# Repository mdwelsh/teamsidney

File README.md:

# sidney-projects

Set up Mac:

sudo easy_install pip
pip install --user pygame

Unicorn HAT Simulator:

https://github.com/jayniz/unicorn-hat-sim

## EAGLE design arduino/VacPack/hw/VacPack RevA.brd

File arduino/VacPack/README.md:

MicroPython on ESP32:
http://docs.micropython.org/en/v1.10/esp32/tutorial/intro.html

Firmware:
https://micropython.org/download/esp32/

```bash
pip install esptool
esptool.py --port /dev/tty.SLAB_USBtoUART erase_flash
esptool.py --chip esp32 --port /dev/tty.SLAB_USBtoUART write_flash -z 0x1000 esp32-idf3-20191220-v1.12.bin
brew install picocom
picocom /dev/tty.SLAB_USBtoUART -b115200

>>> import webrepl_setup
>>> import network
>>> wlan = network.WLAN(network.STA_IF)
>>> wlan.active(True)
>>> wlan.connect('theonet', 'j********')
>>> webrepl.stop()
>>> webrepl.start()
```

Visit:
http://micropython.org/webrepl/#192.168.86.152:8266

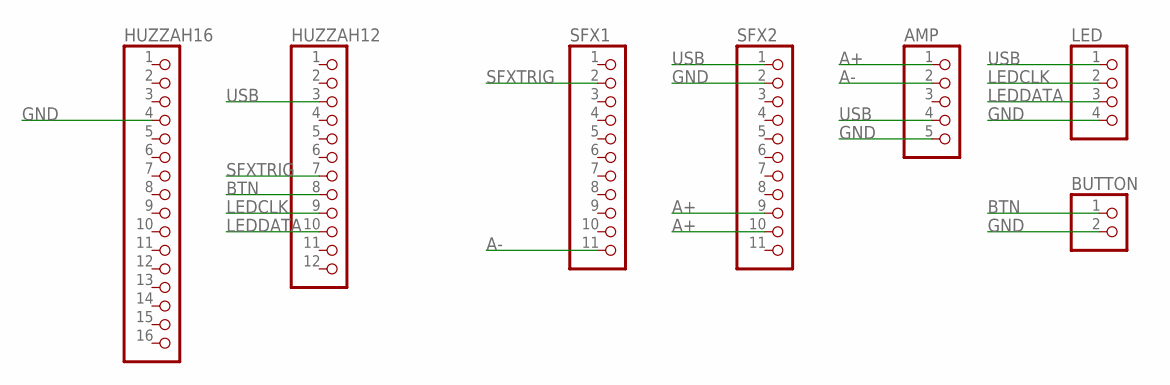
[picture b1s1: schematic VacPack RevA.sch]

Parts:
AMP: PINHD-1X5; 1X05
BUTTON: PINHD-1X2; 1X02
HUZZAH12: PINHD-1X12; 1X12
HUZZAH16: PINHD-1X16; 1X16
LED: PINHD-1X4; 1X04
SFX1, SFX2: PINHD-1X11; 1X11

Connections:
A+: AMP.1, SFX2.9, SFX2.10
A-: AMP.2, SFX1.11
BTN: BUTTON.1, HUZZAH12.8
GND: AMP.5, BUTTON.2, HUZZAH16.4, LED.4, SFX2.2
LEDCLK: HUZZAH12.9, LED.2
LEDDATA: HUZZAH12.10, LED.3
SFXTRIG: HUZZAH12.7, SFX1.2
USB: AMP.4, HUZZAH12.3, LED.1, SFX2.1

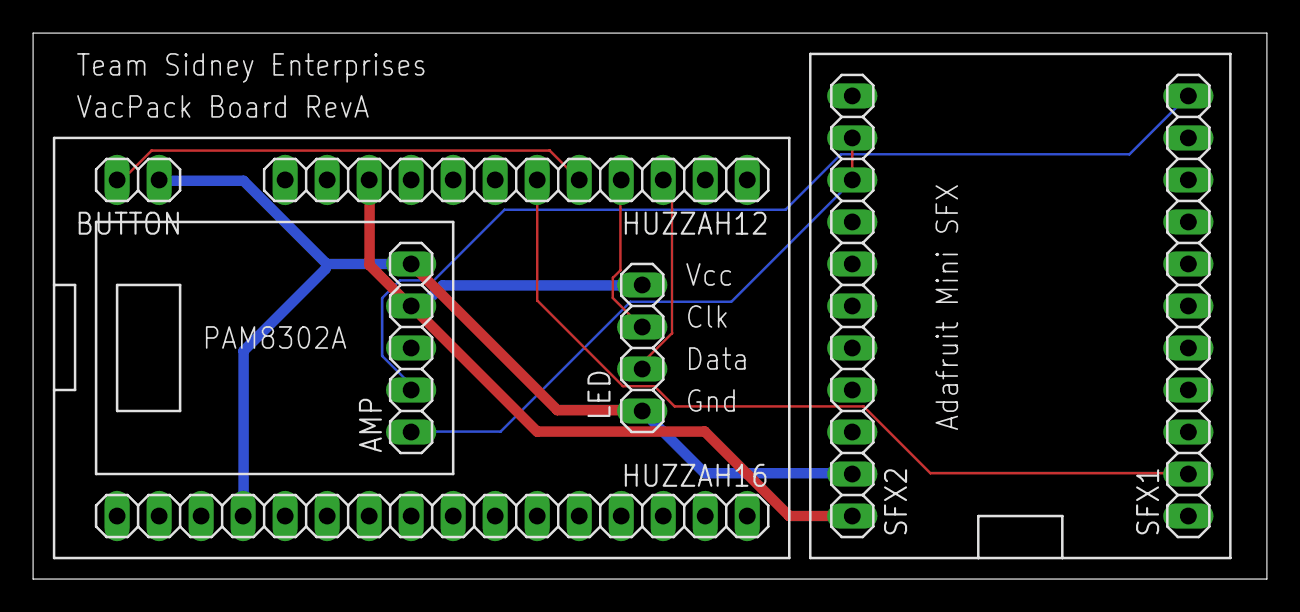
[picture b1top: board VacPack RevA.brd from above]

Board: 2 copper layers, 74.6 x 33.0 mm, 7 parts (0 on the bottom side), 8 nets.

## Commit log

2018-01-20 Basic code for theoclock
2018-01-20 Radar demo
2018-01-23 Adding PNGs
2018-01-23 Fixed rotation
2018-01-23 Scrolling display
2018-01-24 Fading in and out
2018-02-03 Basic clock works
2018-02-03 Comet tail
2018-02-07 Adding new stormtrooper image
2018-02-07 Better comet and new stormtrooper image
2018-02-14 Messing around
2018-02-17 First cut of bomb program
2018-02-18 Adding scrolling time
2018-02-18 Fixes for hardware
2018-02-20 First version of PotFader
2018-02-20 Removing pyc files
2018-02-20 Fixing clock, adding variable brightness, better stormtrooper image
2018-02-21 Show all spans
2018-02-21 Use python3
2018-02-21 Small fixes
2018-03-26 Final PotFader code with HSV to RGB
2018-03-26 Adding Minecraft lamp hw designs
2018-03-28 Adding case designs and stencils
2018-04-03 Adding first version of Lightning code
2018-06-10 New BB-9e mode
2018-06-12 First version of Theo lamp
2018-08-28 First cut at stripsim code
2018-08-30 Sweep code
2018-09-01 Flames
2018-09-11 First cut at this -- polling firebase works
2018-09-11 Added MAC address
2018-09-12 Adding newline
2018-09-13 Checkin and read mode code
2018-09-16 Some basic controls
2018-09-21 Got JSON checkin working
2018-09-21 Renaming HouseLights to Blinky
2018-09-21 Working on revising config logic
2018-09-23 Many updates: - Got JSON parsing working for real. - Added use of freertos tasks - Still need to debug if tasks will properly preempt each other. - Possibly need to change delay's in runConfig to vDe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
2018-09-24 Many changes:
    - Tried to support more reliable blanking of strip.
    The Neopixels (at least) are pretty flaky when I use anything other
    than max brightness, possibly a software problem.
    - Added multitask support. Checkins now run concurrently with strip
    updates.
    - Added strobe, mixBetween, interpolate functions and new "strobe" mode.
2018-09-26 Added comet and rain modes
2018-09-27 Adding README and disabling brightness changes for testing
2018-09-28 Works fine with DotStars and brightness setting
2018-10-06 Add build version to binary
2018-10-07 Adding dotstar feather wing
2018-10-09 Added test mode and random support
2018-10-10 Add RSSI.
2018-10-10 Configure pixel count by web
2018-10-10 Fix bug with rain not using all pixels
2018-10-10 Adding version to checkin
2018-10-10 OTA updates
2018-10-16 Initial geom checkin
2018-10-18 Working on this
2018-10-18 More work
2018-10-20 Adding candle mode
2018-10-20 Adding flicker
2018-10-20 Fix comet
2018-10-21 Adding phantom mode
2018-10-23 Fixing phantoms
2018-10-27 Adding snow, sparkle, halloween modes
2018-11-07 Started working on splat
2018-11-07 Fixed checkin with big JSON payloads
2018-11-07 Multicolor support
2018-12-04 Adding Christmas mode
2018-12-04 Christmas and shimmer modes
2018-12-07 Work on new PixelMapper modes
2018-12-14 Initial version
2018-12-17 Refactored EscherStepper code and added square and circle tests.
2018-12-18 Adding gcode parser
2018-12-18 Got arcs working
2018-12-18 Transition config to struct
2018-12-18 Fixes
2018-12-18 Starting refactoring
2018-12-18 Starting more refactoring work
2018-12-19 Working on computing linear speeds
2018-12-19 Fixed linear path calculation
2018-12-20 Got MultiStepper support working
2018-12-20 Working on refactoring - test and none work.
2018-12-21 Lots of refactorings and new modes.
2018-12-22 Fixed firmware update and some mode tweaks.
2019-01-17 Tweaks for gear reversal and various gcode files.
2019-01-29 Adding zigzag and backlash test code
2019-01-29 Experimental backlash code
2019-02-03 Working on backlash
2019-02-04 Calibration seems to work well
2019-02-04 Cleanups and better Theo Gcode
2019-02-04 Final
2019-02-04 Starting work on web interface
2019-02-04 Cleanups
2019-02-04 Moving this out
2019-02-11 Adding simple Escher
2019-02-11 Checkin works
2019-02-11 Simple HTTP server support
2019-02-12 Working on control protocol
2019-02-12 Basic handlers in place
2019-02-13 Etch start and pause controls
2019-02-15 Task communication works, starting parser
2019-02-15 Parsing and control done.
    However, running steppers from a FreeRTOS task doesn't
    seem to work reliably.
    Likely need to run the steppers from the main loop and ensure
    the other background tasks are idle when etching is happening.
2019-02-15 Etching works fine as long as no other task is running. I think I am going to refactor, get rid of the tasks, just do everything in the main loop.
2019-02-16 Seems to work
2019-02-26 Some fixes
2019-02-27 Pause and ping handlers
2019-03-19 Create LICENSE
2019-04-11 Always reformat flash.
2019-04-11 Fixed PYTHON_E225 issues in arduino/Escher/tools/graphics.py
2019-04-11 Fixed PYTHON_E225 issues in pi/snake/snake.py
2019-05-08 Adding initial checkin. (#4)
2019-05-08 Initial version of person counter.
2019-05-08 Working on text.
2019-05-08 Better fonts and shading
2019-05-08 Better
2019-05-09 Debugging fonts
2019-05-09 More debugging
2019-05-09 Yay! Scrolling works.
2019-05-09 Improvements.
2019-05-09 Person counter demo, first version. (#5)
    * Initial version of person counter.
    * Working on text.
    * Better fonts and shading
    * Better
    * Debugging fonts
    * More debugging
2019-05-13 Formatting.
2019-05-14 Adding Xnor logo.
2019-05-14 Show logo separately.
2019-05-14 Better graphics.
2019-10-27 Adding Space Invaders modes.
2019-11-04 Cleanup.
2019-11-04 Working on cleanups.
2019-11-04 Adding some files.
2019-11-06 Got checkin and readConfig working.
    Next up: Parse JSON in readConfig.
    And do something with it.
2019-11-06 Update to work with latest ArduinoJson library.
2019-11-07 Lots of work on this. Next up:
    - Implement downloadGcodeFile
    - Implement startEtching
    - Modify EscherParser to parse gcode
2019-11-08 Maybe done with the HTTP stuff, just need to patch up the gCode parser.
2019-11-08 Working on gCode parser.
2019-11-11 Adding first version.
2019-11-11 Parser is done -- I think?
    Next up:
    - Try running it end to end with manual commands being entered into
    Firebase.
    - Add back in support for scaling and translation in the UI -- this
    would be offset and scaling parameters passed in on the 'etch'
    command to Firebase.
2019-11-12 Seems to compile.
2019-11-12 Great progress. Some bugs:
    - downloadGcode fails with a stream write error. Might be using that
    API incorrectly.
2019-11-13 This might even work!
2019-12-05 Working on adding offset and scale.
    Also added backlashX and backlashY to command message.
2019-12-05 Working on this. Need to deal with scaleToFit.
2019-12-05 So far this seems to work.
2019-12-07 This appears to be etching, but the scale and offset calculations are clearly wrong.
2019-12-07 Looks like I fixed the issue with doArc.
    Ignoring EscherDeviceConfig.
2019-12-09 Everything seems to work!
2019-12-11 Cleanup and add hardware files.
2020-01-09 Adding first version of MandelbrotSet.
2020-01-09 Adding README.
2020-01-20 Pushing.
2020-01-20 Adding initial version.
2020-01-20 Removing.
2020-01-27 Simple longitudinal test.
2020-04-29 First version.
2020-05-15 Adding some initial test code.
2020-05-21 Pulling things together
2020-08-29 Adding Prometheus files.
2020-08-29 Adding files.
2020-08-29 More details.
2020-09-12 Adding VacPack.ino.
2020-09-27 Add initial training code.
2020-09-27 Adding initial sketch.
2020-09-27 Adding button trigger
2020-09-28 Adding eval
2020-09-28 Add ONNX export.
2020-09-28 Remove old README content.
2020-10-01 More generation fun.
2020-10-02 Adding gen
2020-10-03 This seems to work.
2020-10-04 Some improvements to lighting.
2020-10-04 Adding SFX, final code.
2020-10-04 Add hardware designs.
2020-10-04 Vacpack (#6)
    * Adding files.
    * More details.
    * Adding VacPack.ino.
    * Adding initial sketch.
    * Adding button trigger
    * Adding SFX, final code.
2020-10-04 Fixup.
2020-10-05 Adding all bricks.
2020-10-10 Allbricks generation and improved training with LR schedule.
2020-10-11 Base Arduino version working.
2020-10-11 Basic blink and motor PWM control.
2020-10-11 Fixed period calculation.
2020-10-11 Adding text.
2020-10-12 TSE works.
2020-10-17 Adding earth
2020-10-17 Globe works.
2020-10-18 More images.
2020-10-18 Try DarkNet19.
2020-10-19 Swapping images.
2020-10-19 Adding octoml logo
2020-10-19 Adding octoml
2020-10-19 Train with lower LR.
2020-10-20 Adding bizcat font.
2020-10-21 Updated pin for PCB.
2020-10-21 Working on spherical deformation.
2020-10-22 Add start button
2020-10-31 Hacks
2020-10-31 Adding Blinky runner code.
2020-11-03 Seems to work.
2020-11-15 Fix PWM
2020-11-22 Fixing up earth image
2020-11-23 Added some more images.
2020-11-27 Add some font stuff.
2020-11-28 Some debugging code.
2020-11-28 Remove clock and Wifi stuff.
2020-11-28 Fixed GOL.
2020-11-29 Migrating Mercator to its own repo
2020-12-21 Cleanup
